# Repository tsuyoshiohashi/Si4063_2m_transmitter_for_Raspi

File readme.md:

# Si4063 2m transmitter for Raspi

Transmit a modulated wave in the 144Mhz band using RaspberryPi and an expansion board (si4063 2m radio hat, homemade, see hat directory).

・Frequency can be set from 144 to 146MHz

・The maximum output is 0.1W (20dBm) and can be set in 128 steps.

・CW (Continuous wave), OOK, FSK modulation is possible

・If you want to attach an antenna and actually emit radio waves, you will need an amateur radio license/qualification.

. When operating, be sure to terminate the SMA terminal (J2: RF output terminal). Otherwise, it may break.

# Environment where operation has been confirmed
Raspi3B+　Raspberry Pi OS(bookworm)

You need to install pigpio.

# HAT configuration and operation
As the title says, we use Silicon Labs' Si4063-C.

The SPI is controlled from the Raspi, but it is controlled by itself via GPIO, so there is no need to configure the SPI of the Raspi.
If SPI0 is enabled, please disable it. (Used as GPIO)

Si4063 operates in Direct Async Mode.

Transmission data is passed from the Raspi's GPIO to the Si4063's GPIO, and is transmitted at the same timing without going through the FIFO.

While transmitting, LED2 lights up as an indicator.

# Software
## si4063.py

You can perform simple sending operations by running it from the command line.

````
$ python si4063.py
````

If there are no arguments, display simple help and exit.
The arguments are as follows.

### -c (seconds)
Transmits unmodulated waves for the specified number of seconds. (10 seconds if not specified)
It is used to measure output magnitude, spurious, etc.

The transmission frequency is 144.05MHz by default. (Can be set with variables)

### -f
Transmits FSK modulated wave for about 10 seconds.

The data is 10101010....
The data rate is approximately 1000bps.
The frequency deviation is 8kHz.
These can be set with parameters.

The IC specifications support data rates up to 1Mbps.
I think high-speed communication is possible if you create an accurate baud rate using a timer interrupt. (It's a little difficult in python...)

### -o
Transmits OOK modulated wave for about 10 seconds.

The data is 10101010....
The data rate is approximately 1000bps.
Like FSK, it can be set with parameters.

Please note that si4063const.py is a parameter file. Please put it in the same directory.

## Main methods
si4063.py can be used by importing it into a python program as a module. (This is the original usage)

The main methods are shown below.

### reset()
Reset si4063.
Execute once after turning on the power.

### power_up()
Boot si4063. Use in the order of reset → power_up.

### part_info()
Get the chip number.
````
count, chip_no = si4063.part_info()
````
count: Number of times it took to retrieve (usually it can be read in one time, but if it is too many times, something is happening)

chip_no: Chip number (0x4063)

### set_radio_frequency(frequency)
Set the transmission frequency. The unit is Hz.
There may be an discrepancies of about 2Hz depending on the resolution of the synthesizer.

### set_modem_freq_offset(freq_offset)
Gives an offset to the transmit frequency.
This corrects the error in the crystal's oscillation frequency, but the value seems to vary depending on the modulation method.
The unit is Hz.

### set_pa_pwr_lvl(pwr_lvl)
Set the transmit power. Specify a value between 0x0 and 0x7f.
A graph of setting values and output can be found in Figure 8 of the si4063-C data sheet.

### setup(mod_type, freq_dev)
Configure the IC register settings and set the modulation method.

Specify either MOD_TYPE_OOK, MOD_TYPE_FSK, or MOD_TYPE_CW.

For FSK, the frequency deviation can be specified in Hz.

### start_tx()
Start sending.

### stop_tx()
Stop sending. The internal state is READY.

### tx_data(data)
Set the sending data data(0|1).
In the sending state, it will be reflected immediately.

### get_adc_reading()
Measures the IC power supply voltage and temperature.

````
temp, voltage = si4063.get_adc_reading()
````

The units are °C and V.

Please note that si4063Cconst.py is a parameter file. Please put it in the same directory.

## radio_morse.py

This is a sample app that sends Morse code.
Import and use si4063.py.

Start it by specifying the wpm number as an argument on the command line.

````
$ python radio_morse.py wpm
````

You will be asked to enter a character string, so please enter an alphanumeric character string.

Morse code '.' and '-' are displayed on the console and sent.

Please note that wpm is limited to 5 to 30.

Have A Fun!

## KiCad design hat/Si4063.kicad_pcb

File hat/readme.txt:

The thickness of the board is 1.0mm.

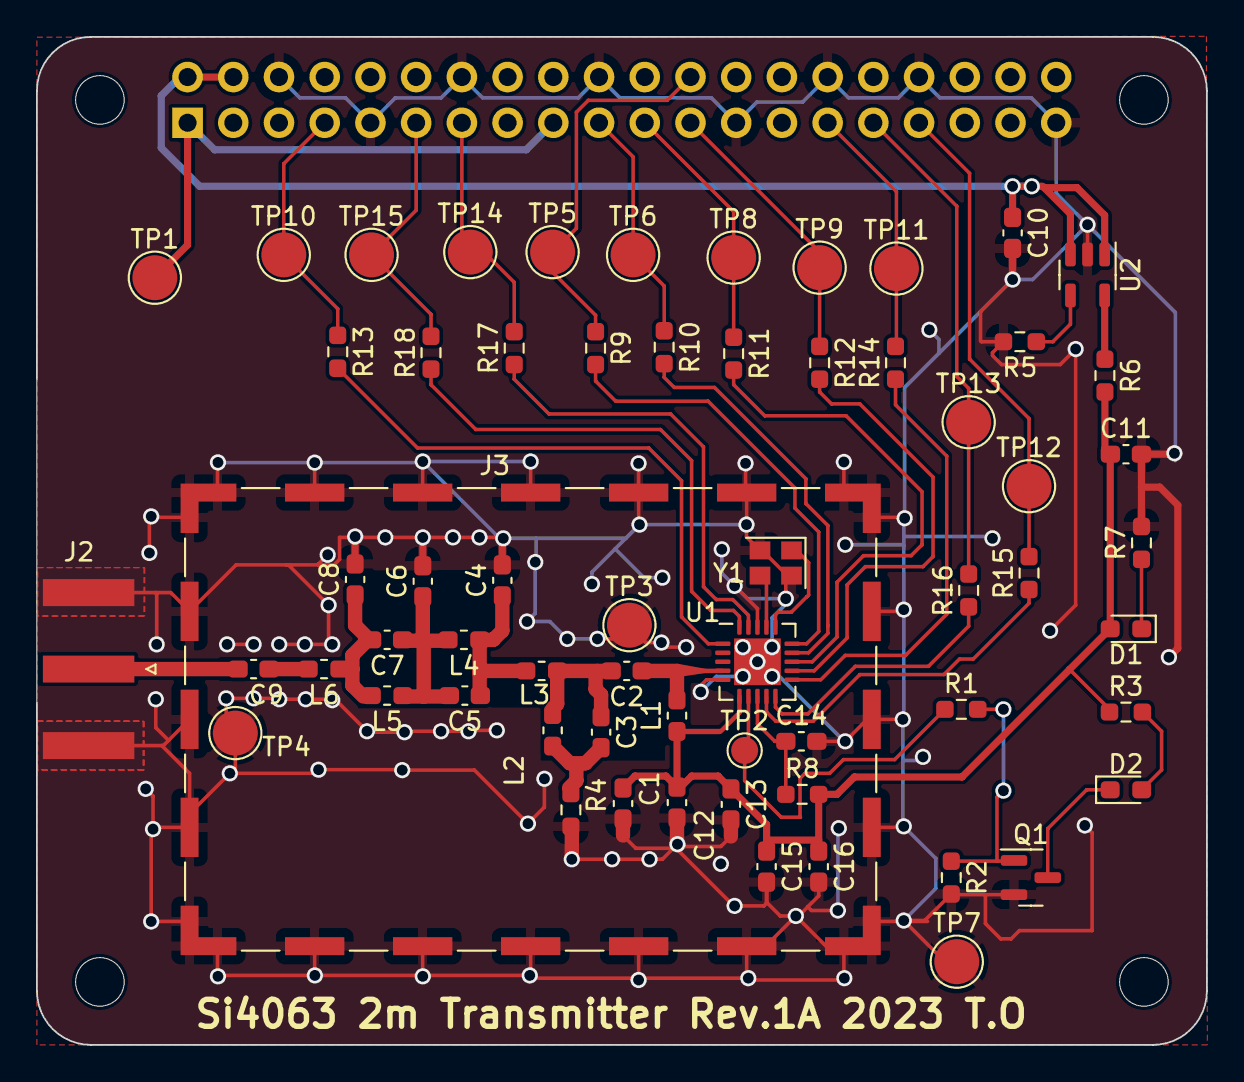
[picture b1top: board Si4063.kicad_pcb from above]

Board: 2 copper layers, 65.0 x 56.0 mm, 68 parts (1 on the bottom side), 42 nets.

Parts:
C7: 2.4pF; C_0603_1608Metric_Pad1.08x0.95mm_HandSolder
C10, C11: 105; C_0603_1608Metric_Pad1.08x0.95mm_HandSolder
C12: 101; C_0603_1608Metric_Pad1.08x0.95mm_HandSolder
C13: 471; C_0603_1608Metric_Pad1.08x0.95mm_HandSolder
C14, C15: 104; C_0603_1608Metric_Pad1.08x0.95mm_HandSolder
C16: 225; C_0603_1608Metric_Pad1.08x0.95mm_HandSolder
C?: 471; C_0603_1608Metric_Pad1.08x0.95mm_HandSolder
C?#2, C?#3: 22pF; C_0603_1608Metric_Pad1.08x0.95mm_HandSolder
C?#4, C?#5: 13pF; C_0603_1608Metric_Pad1.08x0.95mm_HandSolder
C?#6, C?#8: 470pF; C_0603_1608Metric_Pad1.08x0.95mm_HandSolder
C?#7: 3.6pF; C_0603_1608Metric_Pad1.08x0.95mm_HandSolder
D1: PWR; D_0603_1608Metric_Pad1.05x0.95mm_HandSolder
D?: LED; D_0603_1608Metric_Pad1.05x0.95mm_HandSolder
J1: GPIO; PinSocket_2x20_P2.54mm_Vertical
J2: Conn_Coaxial; SMA_Amphenol_132289_EdgeMount
J3: RFShield_TwoPieces; Laird_Technologies_BMI-S-205-F_38.10x25.40mm
L?: 100nH; L_0603_1608Metric_Pad1.05x0.95mm_HandSolder
L?#2: 390nH; L_0603_1608Metric_Pad1.05x0.95mm_HandSolder
L?#3, L?#6: 56nH; L_0603_1608Metric_Pad1.05x0.95mm_HandSolder
L?#4: 82nH; L_0603_1608Metric_Pad1.05x0.95mm_HandSolder
L?#5: 33nH; L_0603_1608Metric_Pad1.05x0.95mm_HandSolder
MH1, MH2, MH3, MH4: MountingHole_2.7mm_M2.5
Q?: Q_NMOS_GSD; SOT-23
R5, R6: 0; R_0603_1608Metric_Pad0.98x0.95mm_HandSolder
R7: 391; R_0603_1608Metric_Pad0.98x0.95mm_HandSolder
R8: 4R7; R_0603_1608Metric_Pad0.98x0.95mm_HandSolder
R9, R13, R14, R15, R16, R17, R18: 47; R_0603_1608Metric_Pad0.98x0.95mm_HandSolder
R10, R11, R12: 39; R_0603_1608Metric_Pad0.98x0.95mm_HandSolder
R?: 2.2k; R_0603_1608Metric_Pad0.98x0.95mm_HandSolder
R?#2: 10k; R_0603_1608Metric_Pad0.98x0.95mm_HandSolder
R?#3: 271; R_0603_1608Metric_Pad0.98x0.95mm_HandSolder
R?#4: 50; R_0603_1608Metric_Pad0.98x0.95mm_HandSolder
TP1: 3.3V; TestPoint_Pad_D2.5mm
TP3, TP4, TP7: GND; TestPoint_Pad_D2.5mm
TP5: nSEL; TestPoint_Pad_D2.5mm
TP6: SDI; TestPoint_Pad_D2.5mm
TP8: SDO; TestPoint_Pad_D2.5mm
TP9: SCLK; TestPoint_Pad_D2.5mm
TP10: SDN; TestPoint_Pad_D2.5mm
TP11: nIRQ; TestPoint_Pad_D2.5mm
TP12: GPIO0; TestPoint_Pad_D2.5mm
TP13: GPIO1; TestPoint_Pad_D2.5mm
TP14: GPIO2; TestPoint_Pad_D2.5mm
TP15: GPIO3; TestPoint_Pad_D2.5mm
TP?: TestPoint; TestPoint_Pad_D1.5mm
U1: Si4063; QFN-20-1EP_4x4mm_P0.5mm_EP2.6x2.6mm
U2: MIC5365-3.3YD5; SOT-23-5
Y1: 30MHz; Crystal_SMD_2520-4Pin_2.5x2.0mm

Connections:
+3.3VA: C11.1, C12.1, C13.1, C15.1, C16.1, C?.1, D1.2 (A), L?#2.1, R6.2, R8.2, R?#3.1, U1.6 (VDD)
+5V: C10.1, J1.2, J1.4, U2.1 (VIN), U2.3 (EN)
/GPIO4_SDN: J1.7, R13.1, TP10.1
/GPIO5_nIRQ: J1.29, R14.2, TP11.1
/GPIO6_GPIO1: J1.31, R16.2, TP13.1
/GPIO13_GPIO0: J1.33, R15.2, TP12.1
/GPIO17_GPIO3: J1.11, R18.2, TP15.1
/GPIO27_GPIO2: J1.13, R17.2, TP14.1
/SPI0.CE0: J1.24, R9.1, TP5.1
/SPI0.MISO: J1.21, R11.1, TP8.1
/SPI0.MOSI: J1.19, R10.1, TP6.1
/SPI0.SCLK: J1.23, R12.1, TP9.1
/power/LED_3.3: D1.1 (K), R7.1
/rf/RF_OUT: C?#8.2, J2.1 (In)
GND: C10.2, C11.2, C12.2, C13.2, C14.2, C15.2, C16.2, C?.2, C?#2.2, C?#3.2, C?#4.2, J1.6, J1.9, J1.14, J1.20, J1.25, J1.30, J1.34, J1.39, J2.2 (Ext), J3.1 (Shield), Q?.2 (S), R5.2, R7.2, R?#2.2, R?#4.2, TP3.1, TP4.1, TP7.1, U1.5 (NC), U1.18 (GND), U1.21 (PADDLE), U2.2 (GND), Y1.2, Y1.4
unnamed: C?#6.1, L?#2.2, U1.4 (TX)
unnamed: C?#5.1, C?#6.2, L?.1, L?#3.1
unnamed: C?#5.2, L?.2, R?#4.1
unnamed: C?#3.1, C?#7.1, L?#3.2, L?#4.1
unnamed: C7.1, C?#2.1, C?#7.2, L?#4.2, L?#6.1
unnamed: C7.2, C?#4.1, L?#5.1, L?#6.2
unnamed: C?#8.1, L?#5.2
unnamed: C14.1, R8.1, U1.8 (VDD)
unnamed: D?.1 (K), Q?.3 (D)
unnamed: D?.2 (A), R?#3.2
unnamed: J1.1, J1.17, TP1.1
unnamed: Q?.1 (G), R?.2, R?#2.1
unnamed: R?.1, TP?.1, U1.7 (TXRAMP)
unnamed: R5.1, U2.4 (NC)
unnamed: R6.1, U2.5 (VOUT)
unnamed: R9.2, U1.15 (nSEL)
unnamed: R10.2, U1.14 (SDI)
unnamed: R11.2, U1.13 (SDO)
unnamed: R12.2, U1.12 (SCLK)
unnamed: R13.2, U1.1 (SDN)
unnamed: R14.1, U1.11 (nIRQ)
unnamed: R15.1, U1.9 (GPIO0)
unnamed: R16.1, U1.10 (GPIO1)
unnamed: R17.1, U1.19 (GPIO2)
unnamed: R18.1, U1.20 (GPIO3)
unnamed: U1.16 (XOUT), Y1.1
unnamed: U1.17 (XIN), Y1.3

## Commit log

2023-12-23 1st commit
2023-12-25 Add image
2023-12-25 Add image2
2023-12-26 add harmonics_image
2023-12-26 edit readme(qualification)
2023-12-27 add pcb info
